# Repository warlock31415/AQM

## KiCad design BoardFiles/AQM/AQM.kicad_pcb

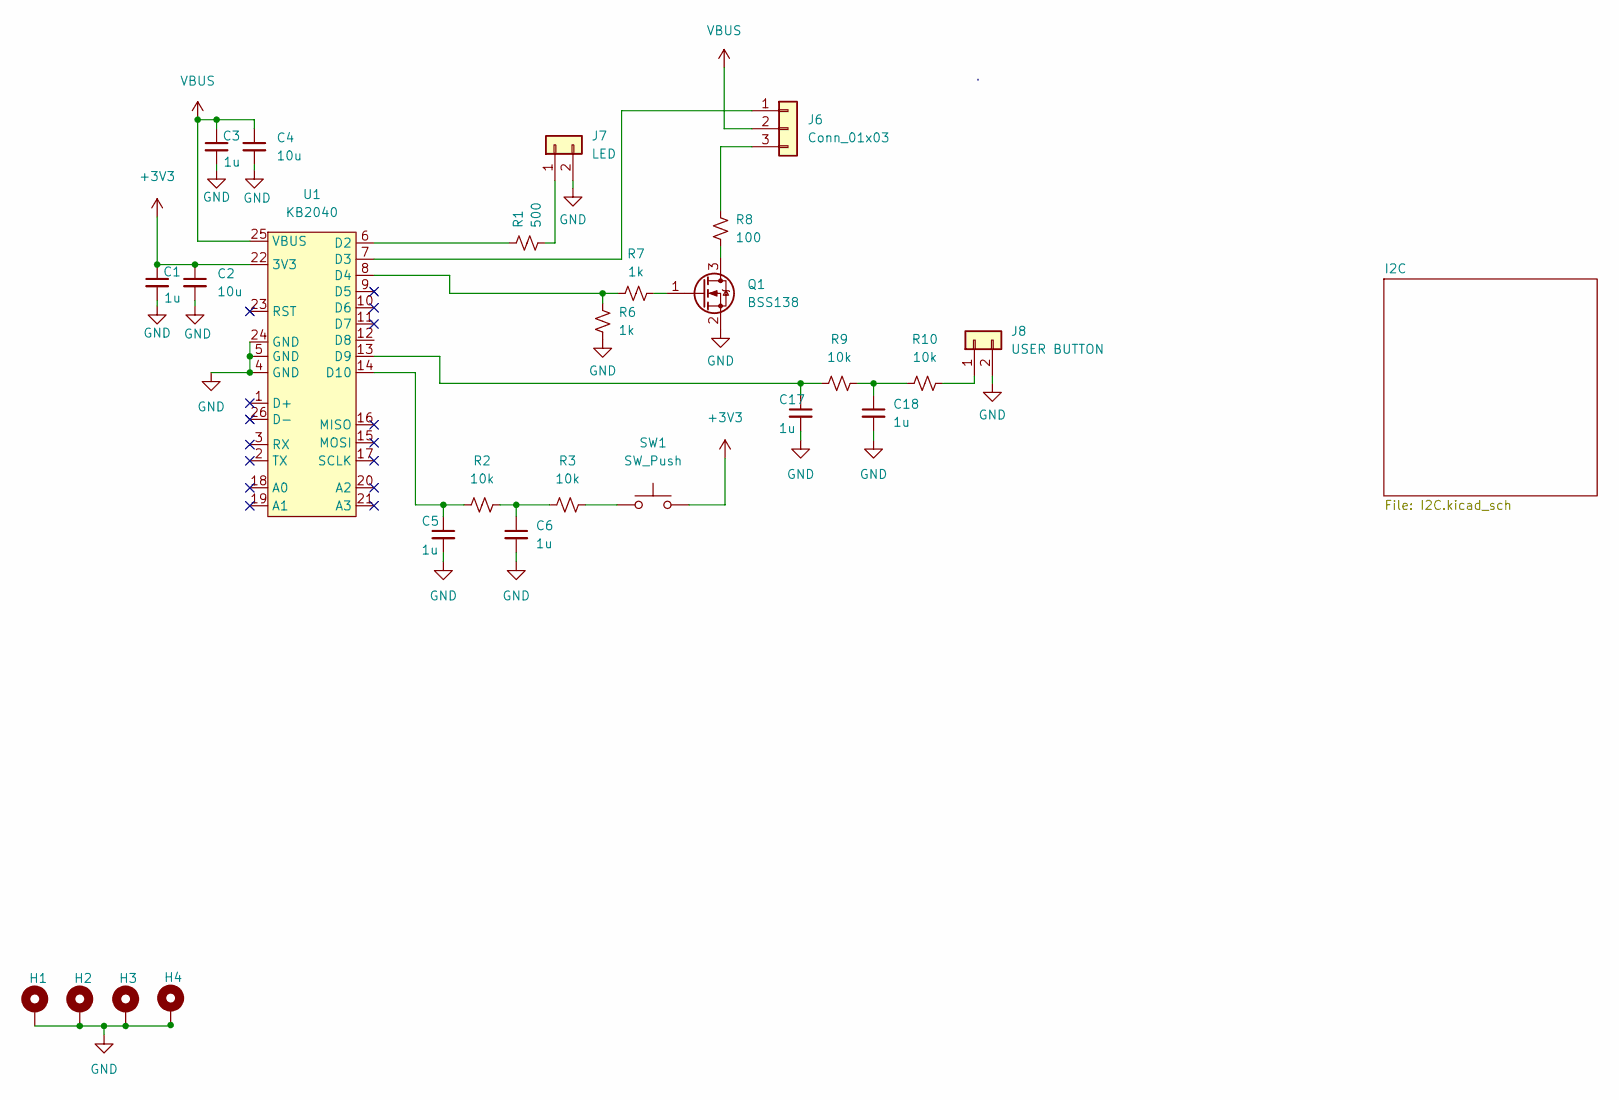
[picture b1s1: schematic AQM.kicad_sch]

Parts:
C1, C3, C5, C6, C17, C18: 1u; C_0805_2012Metric
C2, C4: 10u; C_0805_2012Metric
H1, H2, H3, H4: MountingHole_Pad; MountingHole_3.2mm_M3_DIN965_Pad
J6: Conn_01x03; PinHeader_1x03_P2.54mm_Vertical
J7: LED; PinSocket_1x02_P2.54mm_Vertical
J8: USER BUTTON; PinSocket_1x02_P2.54mm_Vertical
Q1: BSS138; SOT-23
R1: 500; R_0805_2012Metric
R2, R3, R9, R10: 10k; R_0805_2012Metric
R6, R7: 1k; R_0805_2012Metric
R8: 100; R_0805_2012Metric
SW1: SW_Push; SW_PUSH-12mm
U1: KB2040; RPi_KB2040_SMD_TH

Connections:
+3V3: C1.1, C2.1, SW1.2, U1.22 (3V3); also elsewhere on the board
GND: C1.2, C2.2, C3.2, C4.2, C5.2, C6.2, C17.2, C18.2, H1.1, H2.1, H3.1, H4.1, J7.2, J8.2, Q1.2 (S), R6.1, U1.4 (GND), U1.5 (GND), U1.24 (GND); also elsewhere on the board
unnamed: C5.1, R2.1, U1.14 (D10)
unnamed: C6.1, R2.2, R3.1
unnamed: C17.1, R9.1, U1.13 (D9)
unnamed: C18.1, R9.2, R10.1
unnamed: J6.1, U1.7 (D3)
unnamed: J6.3, R8.2
unnamed: J7.1, R1.2
unnamed: J8.1, R10.2
unnamed: Q1.1 (G), R7.2
unnamed: Q1.3 (D), R8.1
unnamed: R1.1, U1.6 (D2)
unnamed: R3.2, SW1.1
unnamed: R6.2, R7.1, U1.8 (D4)
VBUS: C3.1, C4.1, J6.2, U1.25 (VBUS); also elsewhere on the board

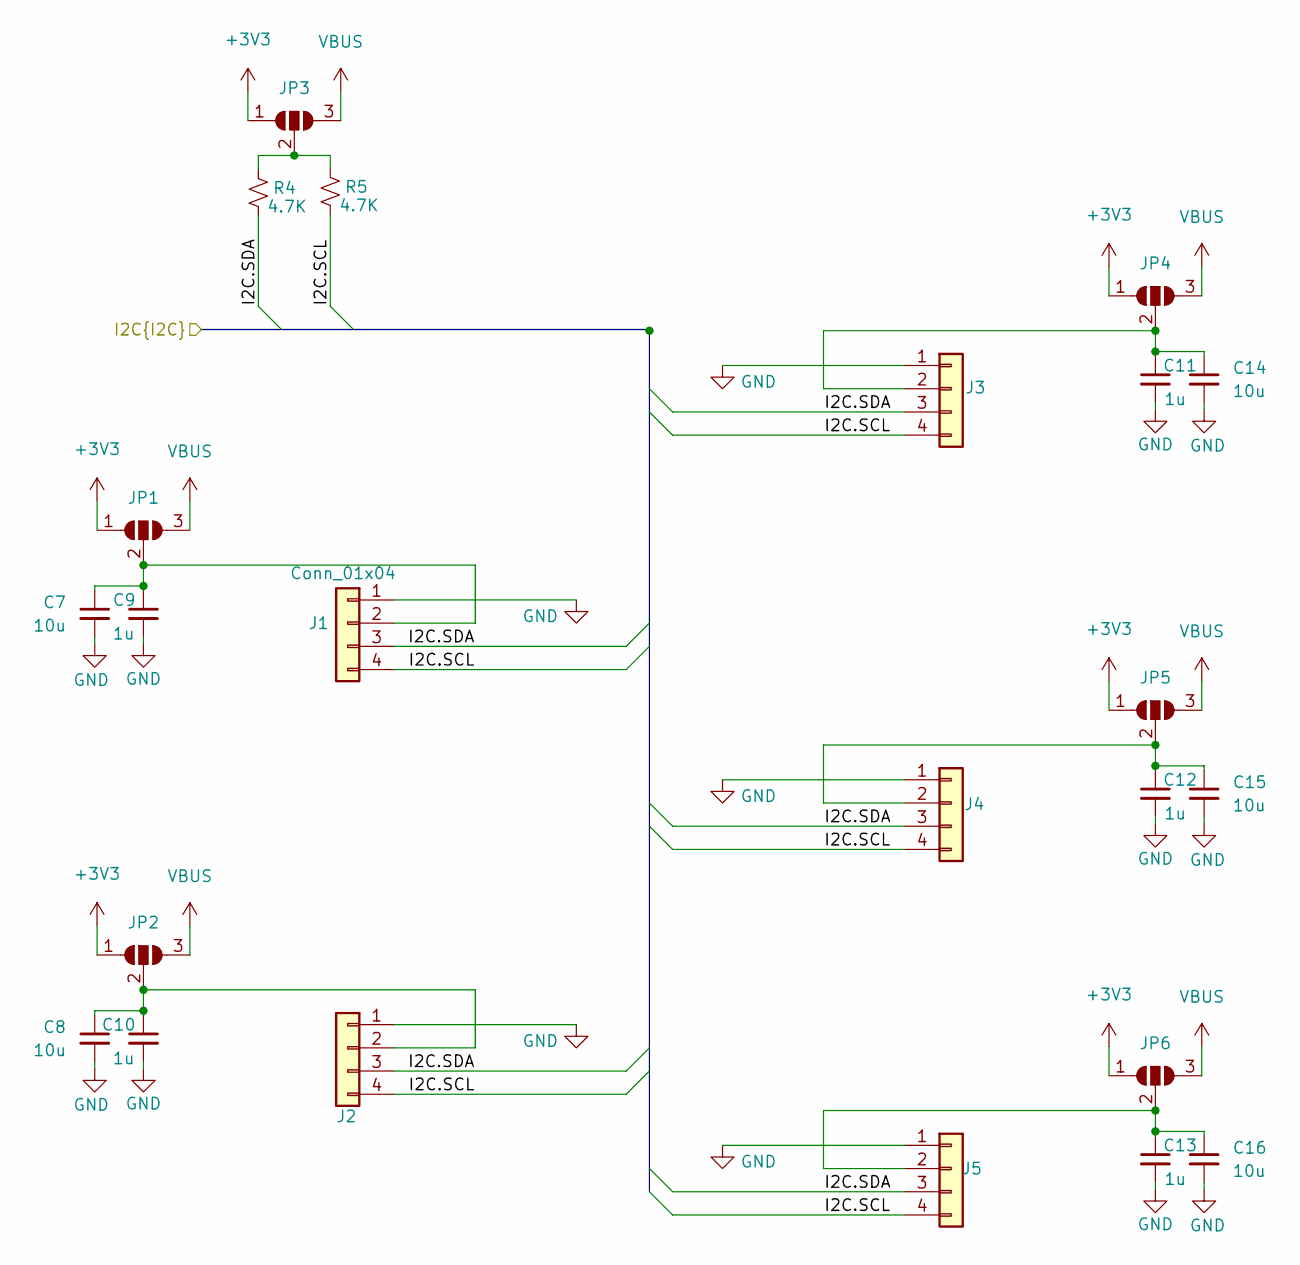
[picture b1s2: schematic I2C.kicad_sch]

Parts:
C7, C8, C14, C15, C16: 10u; C_0805_2012Metric
C9, C10, C11, C12, C13: 1u; C_0805_2012Metric
J1, J2, J3, J4, J5: Conn_01x04; JST_SH_BM04B-SRSS-TB_1x04-1MP_P1.00mm_Vertical
JP1, JP2, JP3, JP4, JP5, JP6: SolderJumper_3_Open; SolderJumper-3_P2.0mm_Open_TrianglePad1.0x1.5mm_NumberLabels
R4, R5: 4.7K; R_0805_2012Metric

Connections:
+3V3: JP1.1 (A), JP2.1 (A), JP3.1 (A), JP4.1 (A), JP5.1 (A), JP6.1 (A); also elsewhere on the board
/I2C/I2C.SCL: J1.4, J2.4, J3.4, J4.4, J5.4, R5.2
/I2C/I2C.SDA: J1.3, J2.3, J3.3, J4.3, J5.3, R4.2
GND: C7.2, C8.2, C9.2, C10.2, C11.2, C12.2, C13.2, C14.2, C15.2, C16.2, J1.1, J2.1, J3.1, J4.1, J5.1; also elsewhere on the board
unnamed: C7.1, C9.1, J1.2, JP1.2 (C)
unnamed: C8.1, C10.1, J2.2, JP2.2 (C)
unnamed: C11.1, C14.1, J3.2, JP4.2 (C)
unnamed: C12.1, C15.1, J4.2, JP5.2 (C)
unnamed: C13.1, C16.1, J5.2, JP6.2 (C)
unnamed: JP3.2 (C), R4.1, R5.1
VBUS: JP1.3 (B), JP2.3 (B), JP3.3 (B), JP4.3 (B), JP5.3 (B), JP6.3 (B); also elsewhere on the board

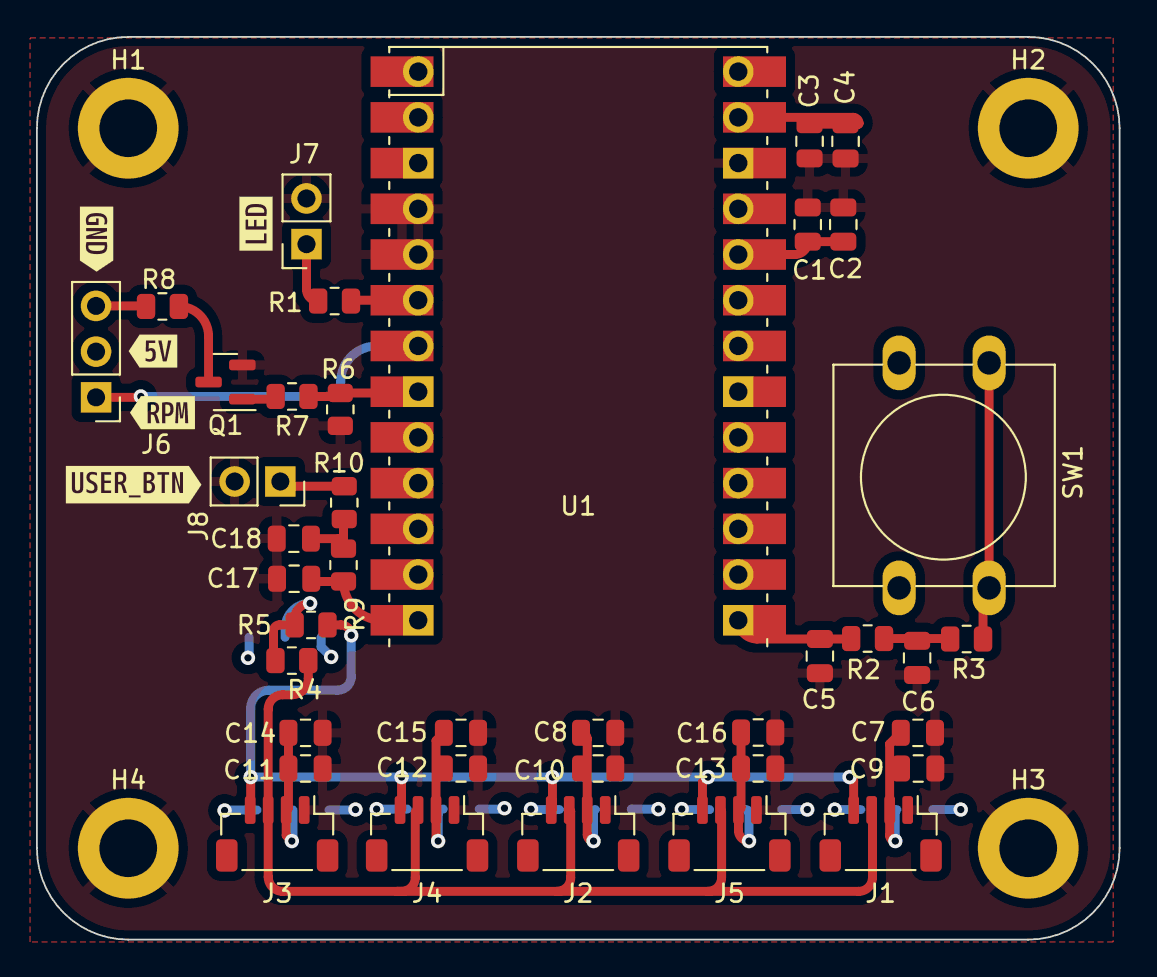
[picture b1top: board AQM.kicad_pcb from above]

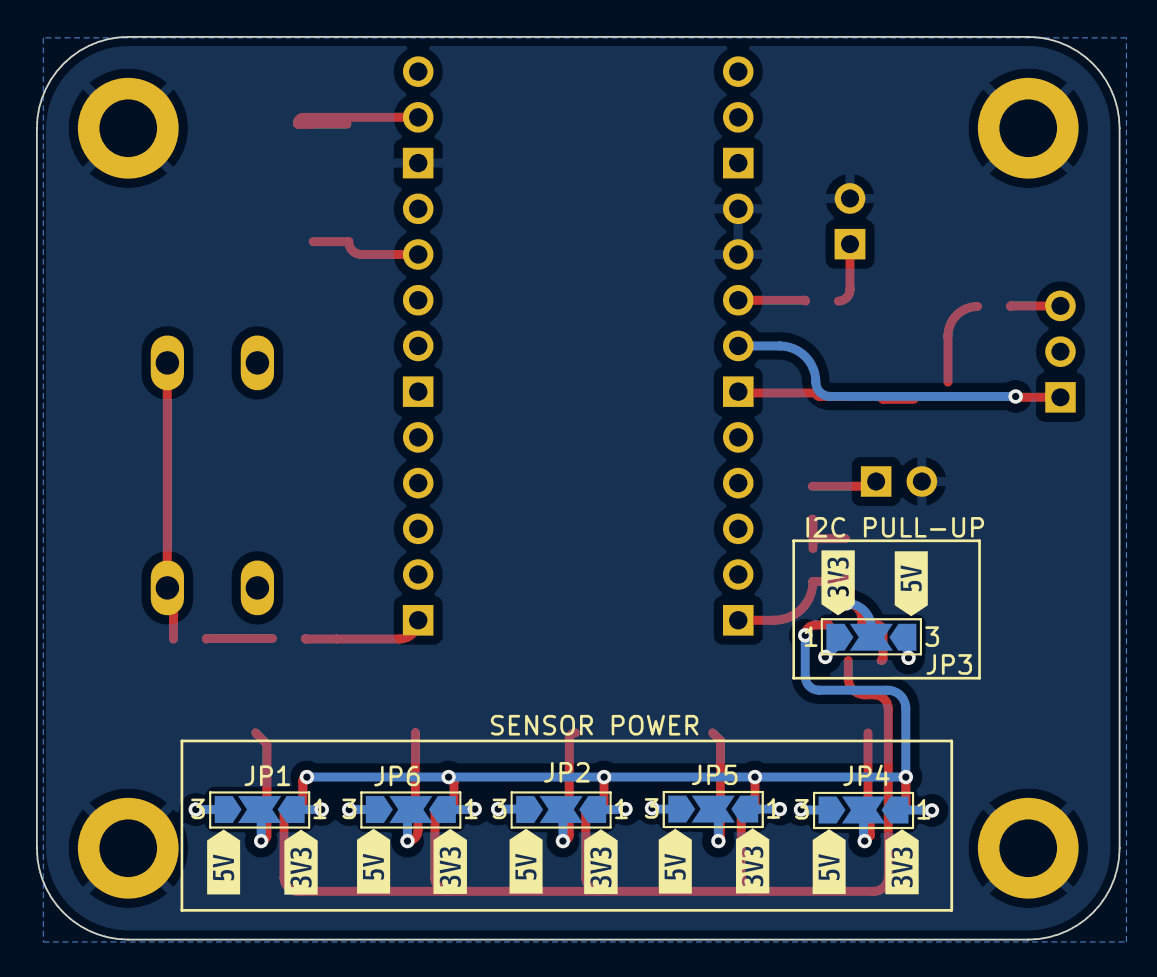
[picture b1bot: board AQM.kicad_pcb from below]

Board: 4 copper layers, 60.2 x 50.2 mm, 66 parts (18 on the bottom side), 24 nets.

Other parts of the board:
kibuzzard-637AF59B: G***; kibuzzard-637AF59B
kibuzzard-637AF633: G***; kibuzzard-637AF633
kibuzzard-637AF646: G***; kibuzzard-637AF646
kibuzzard-6378EB76, kibuzzard-6378EB76#2, kibuzzard-6378EB76#3, kibuzzard-6378EB76#4, kibuzzard-6378EB76#5: G***; kibuzzard-6378EB76
kibuzzard-6378EBEC, kibuzzard-6378EBEC#2, kibuzzard-6378EBEC#3, kibuzzard-6378EBEC#4, kibuzzard-6378EBEC#5: G***; kibuzzard-6378EBEC
kibuzzard-6378ECA4: G***; kibuzzard-6378ECA4
kibuzzard-6378F2ED: G***; kibuzzard-6378F2ED
kibuzzard-6378F9DB: G***; kibuzzard-6378F9DB
kibuzzard-6378F316: G***; kibuzzard-6378F316

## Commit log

2022-11-19 Making the PCB
2022-11-19 Redid copper to make it look pretty
2022-11-19 Redoing Gerbers
2022-11-19 Redoing Gerbers again
2022-11-21 Adding relative paths
2022-11-24 Generating drawings and gerbers
2022-11-24 no clue
2022-11-26 Made things bigger
2022-12-11 Fixing pin swap
2022-12-11 updating Rev
